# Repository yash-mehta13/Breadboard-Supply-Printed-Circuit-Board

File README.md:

# Breadboard Power Supply Module — Custom PCB

A through-hole KiCad design for a breadboard power supply: a DC barrel-jack input, an LM7805 5 V stage, an LM317 stage intended for 3.3 V, and 2.54 mm headers and screw terminals that bring power to a solderless breadboard's rails.

> **Status: design in review — not validated, not fabricated, not tested.** The design files have not been through ERC/DRC, and reading the schematic shows the LM317 (3.3 V) stage's ADJ pin has no connection to ground, so the 3.3 V output is not set as intended. See [Known issues](#known-issues-and-validation-status) before ordering or building anything.

## Contents

- [Intended use](#intended-use)
- [Gallery](#gallery)
- [What the design files confirm](#what-the-design-files-confirm)
- [Block-level description](#block-level-description)
- [Specifications](#specifications)
- [Major components](#major-components)
- [Tools and opening the project](#tools-and-opening-the-project)
- [Known issues and validation status](#known-issues-and-validation-status)
- [Documentation](#documentation)
- [Contributing, licence, attribution](#contributing-licence-attribution)

## Intended use

Prototyping with breadboards usually needs 5 V and/or 3.3 V from a bench or wall DC supply. This board takes a DC input at a barrel jack, regulates it linearly and presents the rails on headers sized to plug into breadboard power rails. Intended for low-power, low-voltage hobby/lab use only.

## Gallery

| | |
|---|---|
|  |  |
| KiCad PCB editor, 2D view: routing on F.Cu (red) and B.Cu (blue) and the board outline with its bottom notch. | KiCad 3D viewer, top: TO-220 regulators, barrel jack, LED, slide switch, headers and terminals. |
|  |  |
| 3D side view: header pin lengths and component heights. | 3D bottom view: hatched GND copper zone and solder side. |

These are KiCad renders, **not photographs of a built board**. They also pre-date the current design files: the 2D view labels R2 as 0.56k and R3 as 0.33k, while `PCB_01.kicad_sch`/`.kicad_pcb` set R2 = 0.33k and R3 = 0.56k. No schematic screenshot exists in the repository.

## What the design files confirm

- Single DC input through barrel jack **J5**, then slide switch **S1**.
- **U1 LM7805** (TO-220) fixed regulator produces the `/5V` net.
- **U2 LM317** (TO-220) adjustable regulator produces the `/3.3V` net (net name only — see issues).
- Two breadboard-rail outputs, `PWR_OUT_TOP` and `PWR_OUT_BOT`. Each can be jumpered to 3.3 V or 5 V on a 3-pin header (J4 / J3) and is exposed on a 2-pin header and a screw terminal (J2/J7 and J1/J6).
- One LED (**D1**) with a series resistor, powered from the switched input net.
- Board outline 53.5 mm × 33.0 mm, two copper layers (F.Cu, B.Cu), 1.6 mm, hatched GND zone on B.Cu, no vias, all through-hole parts.

**Not present in the design:** USB input, AMS1117 regulators, a second LED, any fuse or reverse-polarity protection.

## Block-level description

```
J5 barrel jack -> S1 slide switch -> /12V net (net name only; voltage unspecified)
                                      |-> C1 -> U1 LM7805 -> /5V  (C2 to GND)
                                      |-> U2 LM317 -> /3.3V  (R1 OUT-ADJ, R3 -> D1 cathode net, C3)
                                      '-> R2 -> D1 LED -> R3 -> U2 ADJ
J3 / J4: pin1 3.3V, pin2 rail out, pin3 5V (jumper selects) -> J1+J6 (BOT) / J2+J7 (TOP)
```

Full detail, net list and issues: [docs/circuit-design.md](docs/circuit-design.md).

## Specifications

| Item | Value | Source / status |
|---|---|---|
| Input connector | DC barrel jack with switch contact (`BarrelJack_Horizontal`) | Confirmed (schematic) |
| Input voltage range | **Unspecified** | Design only names the net `/12V`; limits depend on datasheets (not verified here) |
| Input polarity | Pin 1 (tip) → switch; pin 2/3 (sleeve/switch) → GND; no protection | Confirmed; plug polarity must be checked |
| 5 V stage | LM7805 in TO-220 | Confirmed; nominal 5 V from part type, not measured |
| 3.3 V stage | LM317, R1 = 0.33k, R3 = 0.56k | **Defect as drawn**: ADJ has no path to GND; output not 3.3 V by design |
| Output current | **Unspecified / unverified** | Depends on dropout, input voltage, heat sinking; none computed |
| USB input | **None** | Earlier README claim removed |
| Board size | 53.5 mm × 33.0 mm (outline bounding box) | Confirmed (Edge.Cuts) |
| Layers / thickness | 2 / 1.6 mm | Confirmed |
| Track width | 0.2 mm on all segments | Confirmed |
| Design software | KiCad 8.0 (file format `generator_version 8.0`) | Confirmed from files |
| Efficiency, ripple, thermal, EMC | Not measured | Unknown |

## Major components

| Ref | Part | Role |
|---|---|---|
| J5 | Barrel jack with switch | DC input |
| S1 | EG1218 slide switch | Input on/off (pin 3 unused) |
| U1 | LM7805 (TO-220) | 5 V regulator |
| U2 | LM317 (TO-220) | Adjustable regulator for the 3.3 V rail |
| R1, R2 | 0.33k | LM317 OUT–ADJ; LED series |
| R3 | 0.56k | ADJ network |
| C1, C2, C3 | 10 µF, 0.1 µF, 1 µF | Decoupling (see issues) |
| D1 | 5 mm LED | Power indicator |
| J1–J4 | 2.54 mm headers | Rail outputs and 3.3 V/5 V selection |
| J6, J7 | 5.08 mm screw terminals | Rail outputs |

Full list: [docs/bill-of-materials.csv](docs/bill-of-materials.csv) (17 parts, no sourcing data in the design).

## Tools and opening the project

- **KiCad 8.0 or newer** (files were saved by KiCad 8.0; schematic format 20231120, PCB format 20240108). KiCad 7 cannot be assumed to open them; the old README's "KiCad 7" claim was not supported by the files.
- Open `PCB_01.kicad_pro`. Schematic: `PCB_01.kicad_sch`; board: `PCB_01.kicad_pcb`.
- BOM: Schematic Editor → *Tools → Generate Bill of Materials* (or `kicad-cli sch export bom`).
- Fabrication outputs: PCB Editor → *File → Fabrication Outputs* (Gerbers, drill). See [docs/fabrication-and-assembly.md](docs/fabrication-and-assembly.md).
- `sym-lib-table` references a Windows-only absolute path for the `EG1218` library; the symbol and footprint are embedded in the design files, so the project still loads, but KiCad may warn about that library.

## Known issues and validation status

| Check | Status |
|---|---|
| ERC | **Not run** (`kicad-cli` unavailable in the review environment) |
| DRC | **Not run** |
| Schematic ↔ PCB net comparison | Done by script for the reference/pad nets: consistent |
| Gerber review | Not done |
| Bench test | Not done; no evidence the board was ever built |

Open design concerns (details in [docs/circuit-design.md](docs/circuit-design.md)):

1. **LM317 ADJ not connected to GND.** R1 (OUT–ADJ) and R3 meet at ADJ, but R3's other end goes to the LED cathode net, not ground. No resistor to ground exists. The output voltage is therefore not defined by the intended divider.
2. **LED sits in the ADJ network** (12 V → R2 → D1 → R3 → ADJ) rather than being an indicator on a rail.
3. **C3 (1 µF)** connects /3.3V to the LED cathode net, not to GND. The 3.3 V rail has no capacitor to ground.
4. No reverse-polarity or over-voltage protection; no heatsinks; only 0.2 mm traces everywhere.
5. Capacitors use a ceramic disc footprint including the 10 µF part.

Do not fabricate or power this design before the owner reviews these. See [docs/validation-and-testing.md](docs/validation-and-testing.md) and [docs/safety-and-limitations.md](docs/safety-and-limitations.md).

## Documentation

[Project overview](docs/project-overview.md) · [Circuit design](docs/circuit-design.md) · [BOM](docs/bill-of-materials.csv) · [Fabrication & assembly](docs/fabrication-and-assembly.md) · [Validation & testing](docs/validation-and-testing.md) · [Safety & limitations](docs/safety-and-limitations.md) · [Roadmap](docs/roadmap.md) · [Licensing](docs/licensing.md) · [Changelog](CHANGELOG.md)

## Contributing, licence, attribution

See [CONTRIBUTING.md](CONTRIBUTING.md). **No licence file exists yet**, so all rights are reserved by default; see [docs/licensing.md](docs/licensing.md).

Design by [@yash-mehta13](https://github.com/yash-mehta13).

Suggested topics: `kicad` `pcb-design` `breadboard-power-supply` `lm317` `lm7805` `linear-regulator` `through-hole` `open-hardware`

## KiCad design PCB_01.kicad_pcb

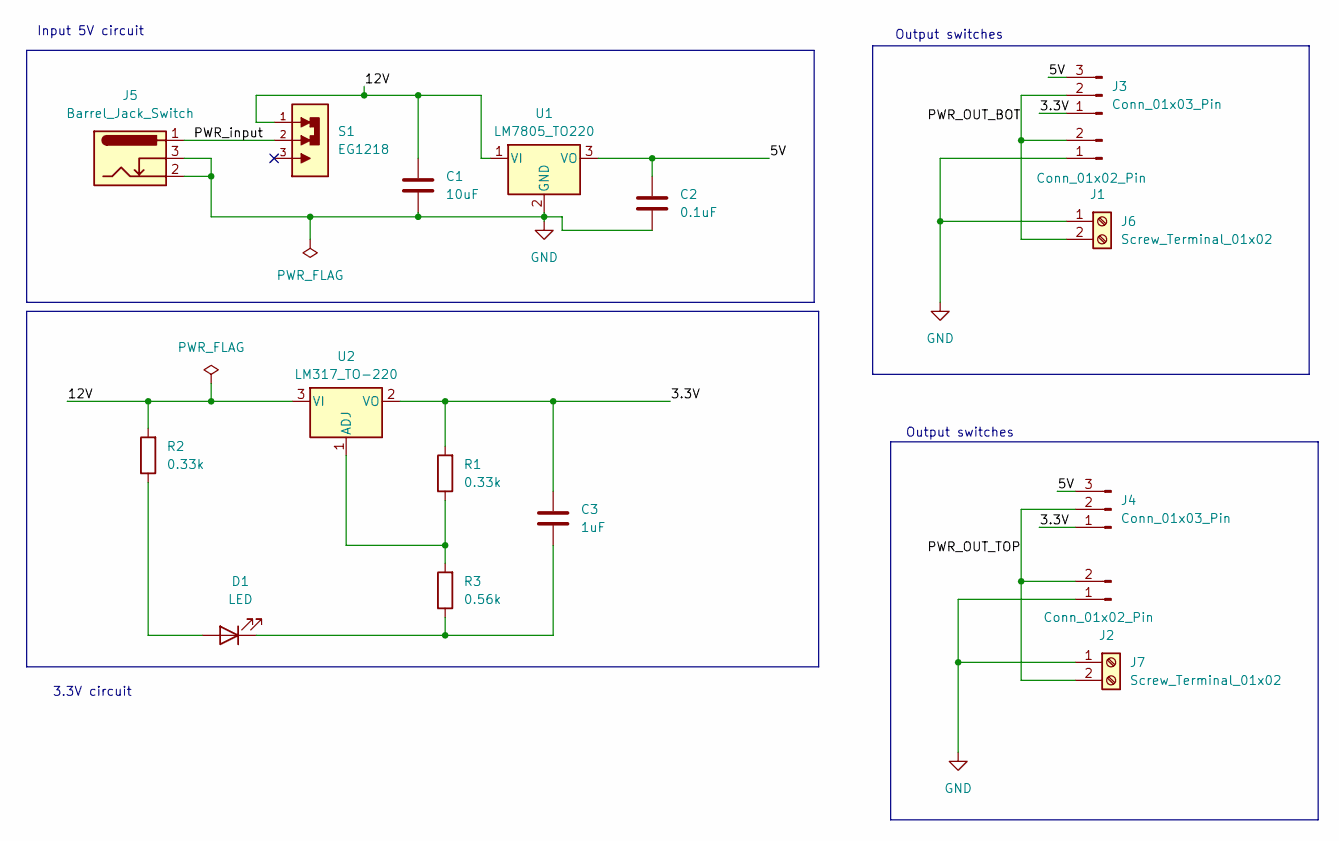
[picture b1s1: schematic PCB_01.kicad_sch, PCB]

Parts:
C1: 10uF; C_Disc_D3.0mm_W1.6mm_P2.50mm
C2: 0.1uF; C_Disc_D3.0mm_W1.6mm_P2.50mm
C3: 1uF; C_Disc_D3.0mm_W1.6mm_P2.50mm
D1: LED; LED_D5.0mm
J1, J2: Conn_01x02_Pin; PinHeader_1x02_P2.54mm_Vertical
J3, J4: Conn_01x03_Pin; PinHeader_1x03_P2.54mm_Vertical
J5: Barrel_Jack_Switch; BarrelJack_Horizontal
J6, J7: Screw_Terminal_01x02; TerminalBlock_bornier-2_P5.08mm
R1, R2: 0.33k; R_Axial_DIN0204_L3.6mm_D1.6mm_P7.62mm_Horizontal
R3: 0.56k; R_Axial_DIN0204_L3.6mm_D1.6mm_P7.62mm_Horizontal
S1: EG1218; SW_EG1218
U1: LM7805_TO220; TO-220-3_Vertical
U2: LM317_TO-220; TO-220-3_Vertical

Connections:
/3.3V: C3.1, J3.1, J4.1, R1.2, U2.2 (VO)
/5V: C2.1, J3.3, J4.3, U1.3 (VO)
/12V: C1.1, R2.2, S1.1, U1.1 (VI), U2.3 (VI)
/PWR_OUT_BOT: J1.2, J3.2, J6.2
/PWR_OUT_TOP: J2.2, J4.2, J7.2
/PWR_input: J5.1, S1.2
GND: C1.2, C2.2, J1.1, J2.1, J5.2, J5.3, J6.1, J7.1, U1.2 (GND)
unnamed: D1.2 (A), R2.1
unnamed: C3.2, D1.1 (K), R3.1
unnamed: R1.1, R3.2, U2.1 (ADJ)

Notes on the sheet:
Input 5V circuit
Output switches
3.3V circuit

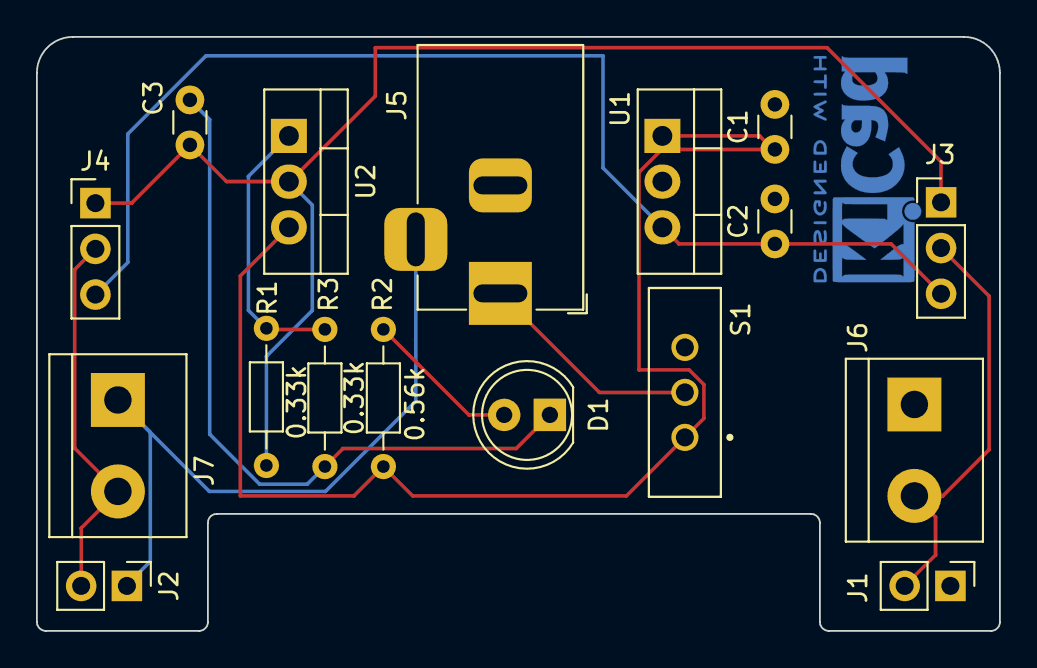
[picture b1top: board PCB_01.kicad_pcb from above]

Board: 2 copper layers, 53.5 x 33.0 mm, 17 parts (0 on the bottom side), 10 nets.

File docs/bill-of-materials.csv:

Reference,Qty,Value,Footprint,Description,Datasheet (as set in schematic),Manufacturer,MPN,Supplier,Supplier PN,Populate,Notes
C1,1,10uF,Capacitor_THT:C_Disc_D3.0mm_W1.6mm_P2.50mm,Capacitor on switched input rail (/12V) to GND,,,,,,Yes,Dielectric/voltage rating not specified in design. A 10uF part in a 3.0mm disc footprint should be checked for availability
C2,1,0.1uF,Capacitor_THT:C_Disc_D3.0mm_W1.6mm_P2.50mm,Capacitor on 5V output of U1 to GND,,,,,,Yes,Voltage rating not specified in design
C3,1,1uF,Capacitor_THT:C_Disc_D3.0mm_W1.6mm_P2.50mm,Capacitor between /3.3V and Net-(D1-K) (NOT GND as drawn),,,,,,Yes,See docs/circuit-design.md section 'Issues'. Voltage rating not specified
D1,1,LED,LED_THT:LED_D5.0mm,5mm through-hole LED,,,,,,Yes,Colour not specified in design (3D render shows red)
J1;J2,2,Conn_01x02_Pin,Connector_PinHeader_2.54mm:PinHeader_1x02_P2.54mm_Vertical,2-pin 2.54mm header: GND + breadboard rail (J1 = PWR_OUT_BOT; J2 = PWR_OUT_TOP),,,,,,Yes,Pin 1 GND (square pad)
J3;J4,2,Conn_01x03_Pin,Connector_PinHeader_2.54mm:PinHeader_1x03_P2.54mm_Vertical,3-pin 2.54mm header: pin1 3.3V / pin2 rail output / pin3 5V (J3 = PWR_OUT_BOT; J4 = PWR_OUT_TOP),,,,,,Yes,Rail source chosen by a jumper (jumper not in BOM)
J5,1,Barrel_Jack_Switch,Connector_BarrelJack:BarrelJack_Horizontal,DC barrel jack with switch contact,,,,,,Yes,Plug size/current rating not specified in design
J6;J7,2,Screw_Terminal_01x02,TerminalBlock:TerminalBlock_bornier-2_P5.08mm,2-way 5.08mm screw terminal: GND + rail output (J6 = PWR_OUT_BOT; J7 = PWR_OUT_TOP),,,,,,Yes,Pin 1 GND (square pad)
R1;R2,2,0.33k,Resistor_THT:R_Axial_DIN0204_L3.6mm_D1.6mm_P7.62mm_Horizontal,Resistor 330 ohm (R1: LM317 OUT-to-ADJ; R2: LED series),,,,,,Yes,Power rating/tolerance not specified
R3,1,0.56k,Resistor_THT:R_Axial_DIN0204_L3.6mm_D1.6mm_P7.62mm_Horizontal,Resistor 560 ohm (between U2 ADJ and Net-(D1-K)),,,,,,Yes,Power rating/tolerance not specified
S1,1,EG1218,EG1218:SW_EG1218,3-pin slide switch (custom symbol/footprint library),,,,,,Yes,Pin 3 intentionally unconnected. Footprint embedded in PCB; symbol embedded in schematic
U1,1,LM7805_TO220,Package_TO_SOT_THT:TO-220-3_Vertical,5V fixed linear regulator,https://www.onsemi.cn/PowerSolutions/document/MC7800-D.PDF,,,,,Yes,Manufacturer/MPN not specified; no heatsink in design
U2,1,LM317_TO-220,Package_TO_SOT_THT:TO-220-3_Vertical,Adjustable linear regulator (3.3V stage),http://www.ti.com/lit/ds/symlink/lm317.pdf,,,,,Yes,Manufacturer/MPN not specified; no heatsink in design. See circuit issue on ADJ network

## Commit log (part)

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2025-06-20 README.md
